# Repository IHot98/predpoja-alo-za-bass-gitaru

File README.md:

Predpojačalo za bass gitaru
---

***
Maturalni rad iz srednje škole 
Rađeno 2017. godine

Predpojačalo rastavljeno na više PCB-a radi modularnosti
***

slika pojačala u fazi izrade

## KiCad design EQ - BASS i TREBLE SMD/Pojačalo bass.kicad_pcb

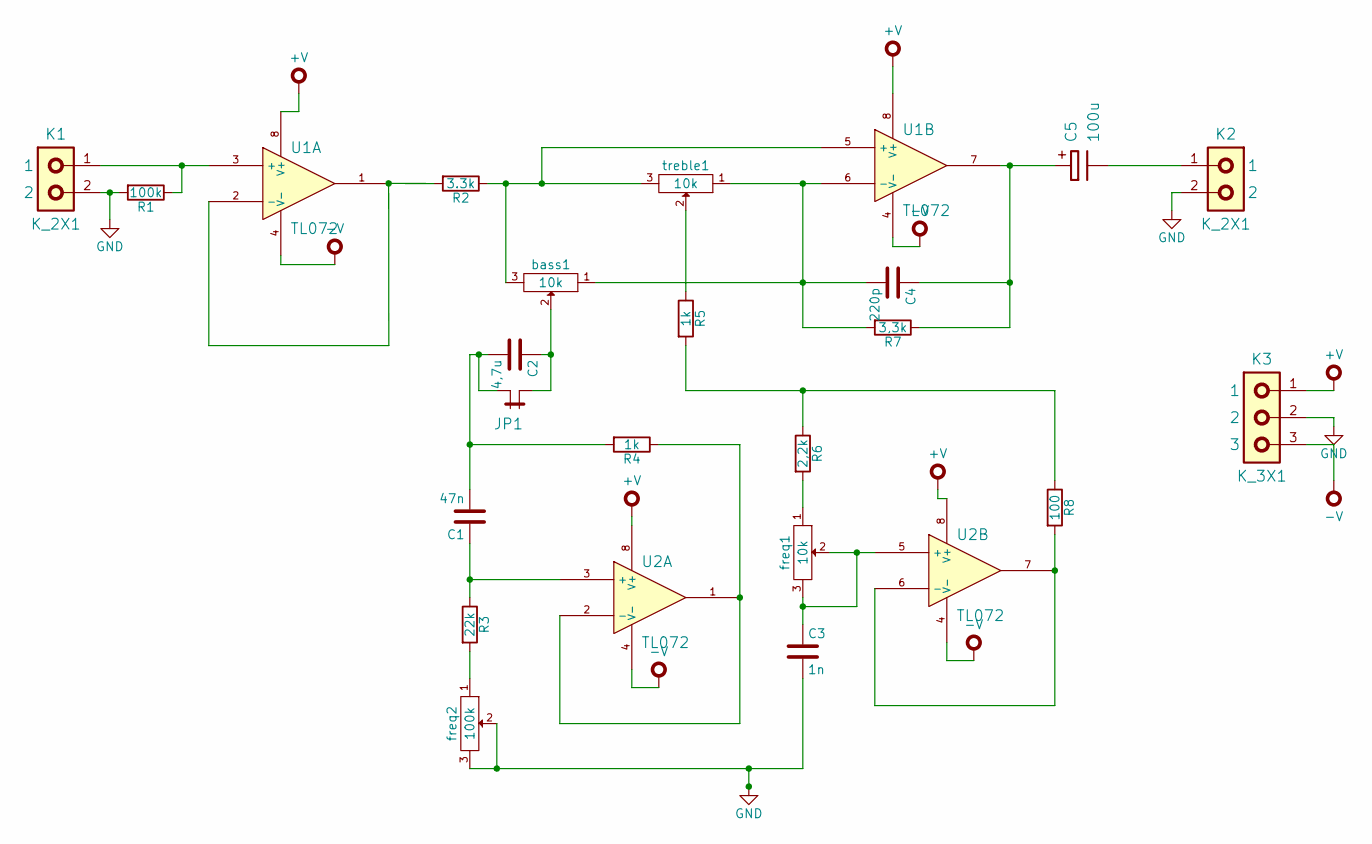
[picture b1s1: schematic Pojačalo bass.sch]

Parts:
C1: 47n; C_R5_D2,5X7,2
C2: 4,7u; C_R5_D2,5X7,2
C3: 1n; C_R5_D2,5X7,2
C4: 220p; C_R5_D2,5X7,2
C5: 100u; CPOL_R5_D6,35
JP1: JP; K_2X1_VERT_KV_R2,54
K1, K2: K_2X1; K_2x1
K3: K_3X1; K_3X1_VERT_KV_R2,54
R1: 100k; R_SMD_0805_NoSilk
R2: 3.3k; R_SMD_0805_NoSilk
R3: 22k; R_SMD_0805_NoSilk
R4, R5: 1k; R_SMD_0805_NoSilk
R6: 2,2k; R_SMD_0805_NoSilk
R7: 3,3k; R_SMD_0805_NoSilk
R8: 100; R_SMD_0805_NoSilk
U1, U2: TL072; DIP-8
bass1: 10k; K_3x1_PIN_R2,54
freq1: 10k; K_3x1_PIN_R2,54
freq2: 100k; K_3x1_PIN_R2,54
treble1: 10k; K_3x1_PIN_R2,54

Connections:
+V: K3.1, U1.8 (V+), U2.8 (V+)
-V: K3.3, U1.4 (V-), U2.4 (V-)
GND: C3.2, K1.2, K2.2, K3.2, R1.2, freq2.2, freq2.3
unnamed: C1.1, R3.1, U2.3 (+)
unnamed: C1.2, C2.2, JP1.2, R4.2
unnamed: C2.1, JP1.1, bass1.2
unnamed: C3.1, U2.5 (+), freq1.2, freq1.3
unnamed: C4.1, C5.+, R7.1, U1.7
unnamed: C4.2, R7.2, U1.6 (-), bass1.1, treble1.1
unnamed: C5.-, K2.1
unnamed: K1.1, R1.1, U1.3 (+)
unnamed: R2.1, U1.5 (+), bass1.3, treble1.3
unnamed: R2.2, U1.1, U1.2 (-)
unnamed: R3.2, freq2.1
unnamed: R4.1, U2.1, U2.2 (-)
unnamed: R5.1, treble1.2
unnamed: R5.2, R6.1, R8.1
unnamed: R6.2, freq1.1
unnamed: R8.2, U2.6 (-), U2.7

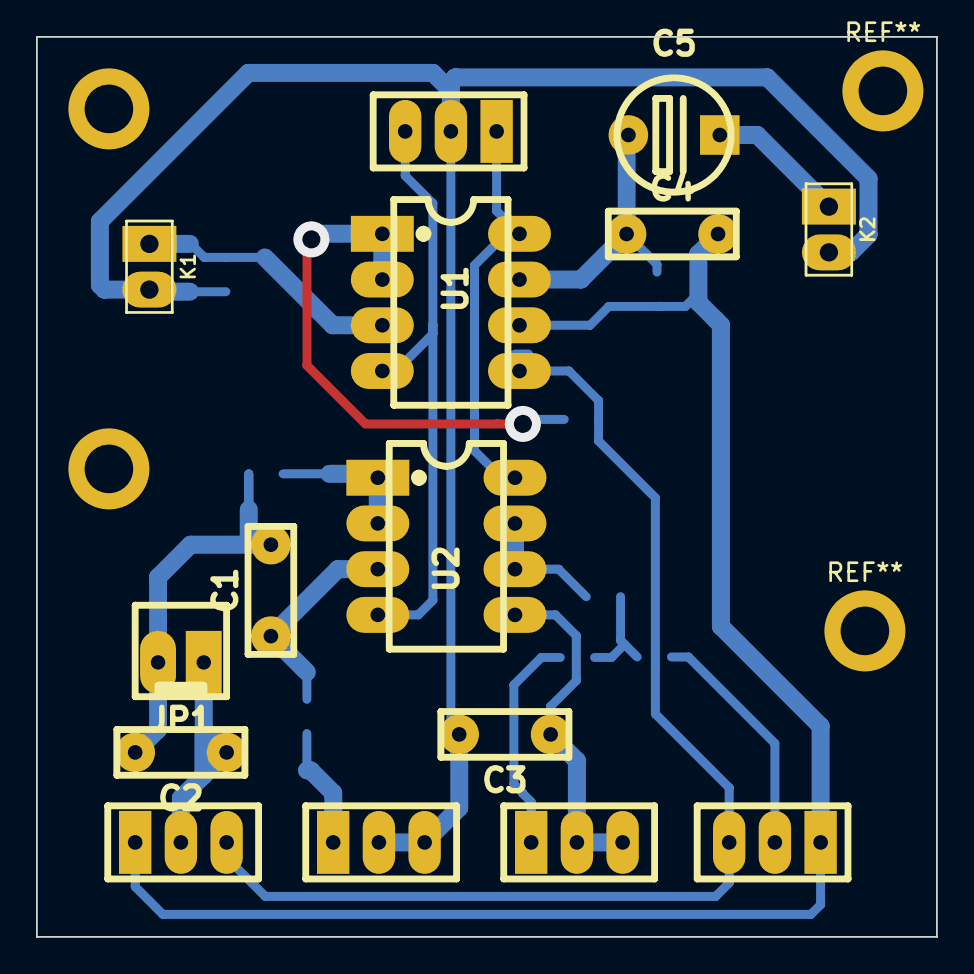
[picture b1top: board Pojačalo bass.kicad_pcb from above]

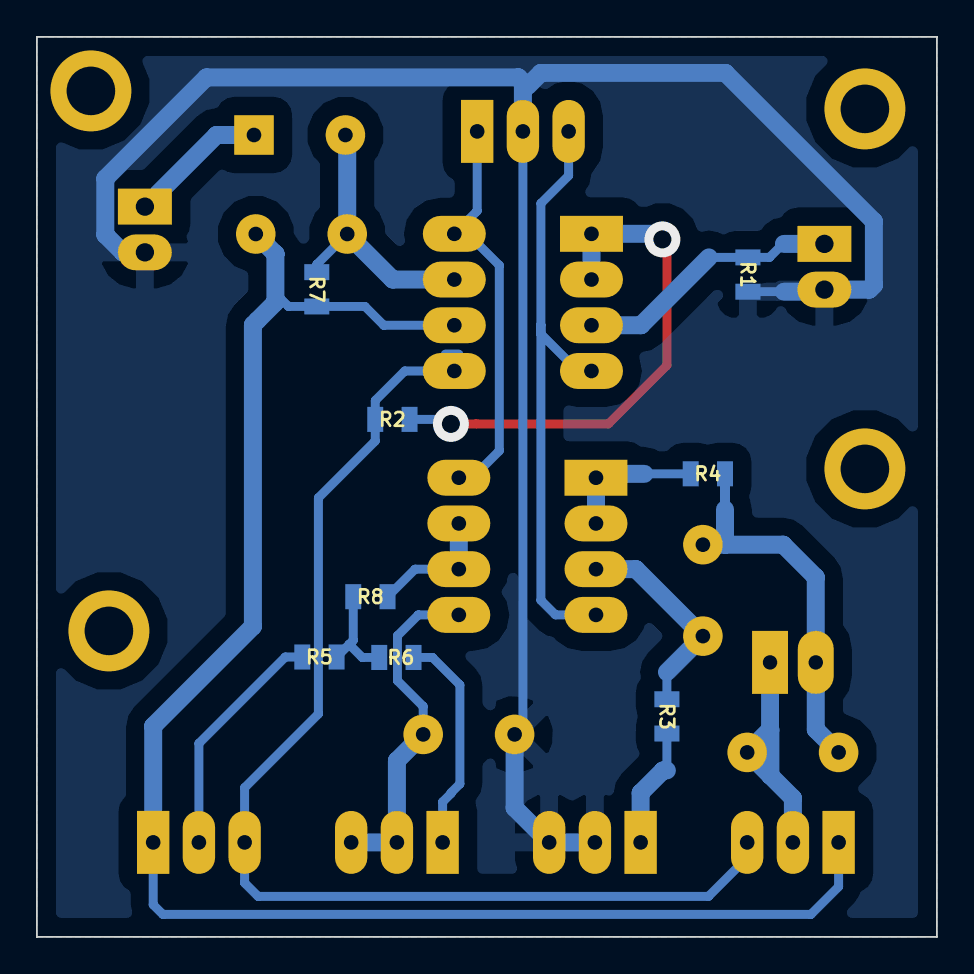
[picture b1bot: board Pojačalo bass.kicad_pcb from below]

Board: 2 copper layers, 50.0 x 50.0 mm, 23 parts (8 on the bottom side), 19 nets.

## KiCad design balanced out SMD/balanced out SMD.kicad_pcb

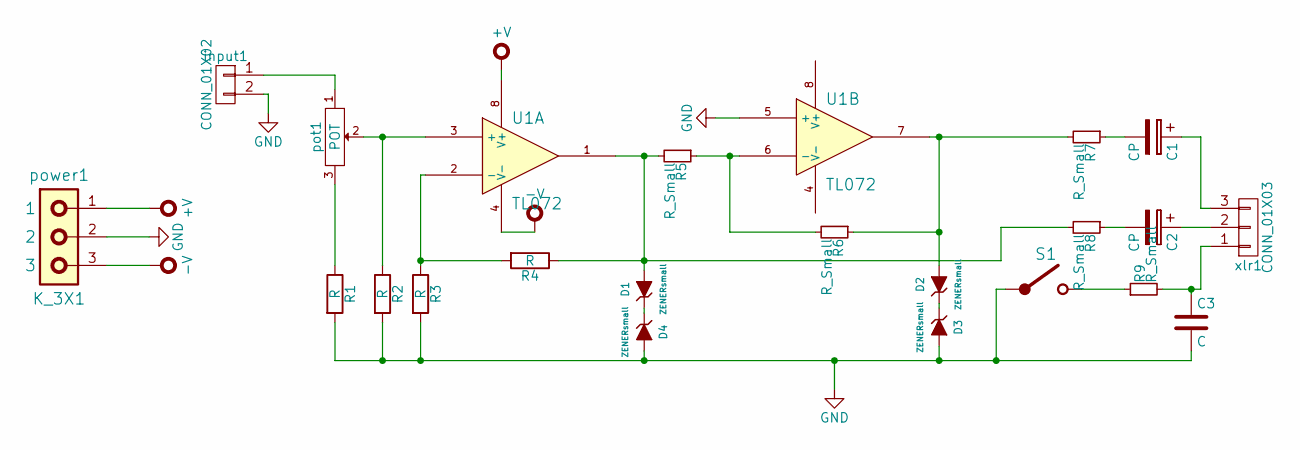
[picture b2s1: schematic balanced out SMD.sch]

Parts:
C1, C2: CP; C_Radial_D5_L6_P2.5
C3: C; C_Radial_D5_L6_P2.5
D1, D2, D3, D4: ZENERsmall; Diode_DO-35_SOD27_Horizontal_RM10
R1, R2, R3, R4: R; R_SMD_0805_NoSilk
R5, R6, R7, R8: R_Small; R_SMD_0805_NoSilk
R9: R_Small; R_MF_0,6W_R10
S1: S_1; K_2X1_VERT_KV_R2,54
U1: TL072; DIP-8
input1: CONN_01X02; K_2X1_VERT_KV_R2,54
pot1: POT; K_3X1_VERT_KV_R2,54
power1: K_3X1; K_3X1_VERT_KV_R2,54
xlr1: CONN_01X03; K_3X1_VERT_KV_R2,54

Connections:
+V: U1.8 (V+), power1.1
-V: U1.4 (V-), power1.3
GND: C3.2, D3.2 (A), D4.2 (A), R1.2, R2.2, R3.2, S1.1, U1.5 (+), input1.2, power1.2
unnamed: C1.1, xlr1.3
unnamed: C1.2, R7.1
unnamed: C2.1, xlr1.2
unnamed: C2.2, R8.1
unnamed: C3.1, R9.2, xlr1.1
unnamed: D1.1 (K), D4.1 (K)
unnamed: D1.2 (A), R4.1, R5.2, R8.2, U1.1
unnamed: D2.1 (K), D3.1 (K)
unnamed: D2.2 (A), R6.1, R7.2, U1.7
unnamed: R1.1, pot1.3
unnamed: R2.1, U1.3 (+), pot1.2
unnamed: R3.1, R4.2, U1.2 (-)
unnamed: R5.1, R6.2, U1.6 (-)
unnamed: R9.1, S1.2
unnamed: input1.1, pot1.1

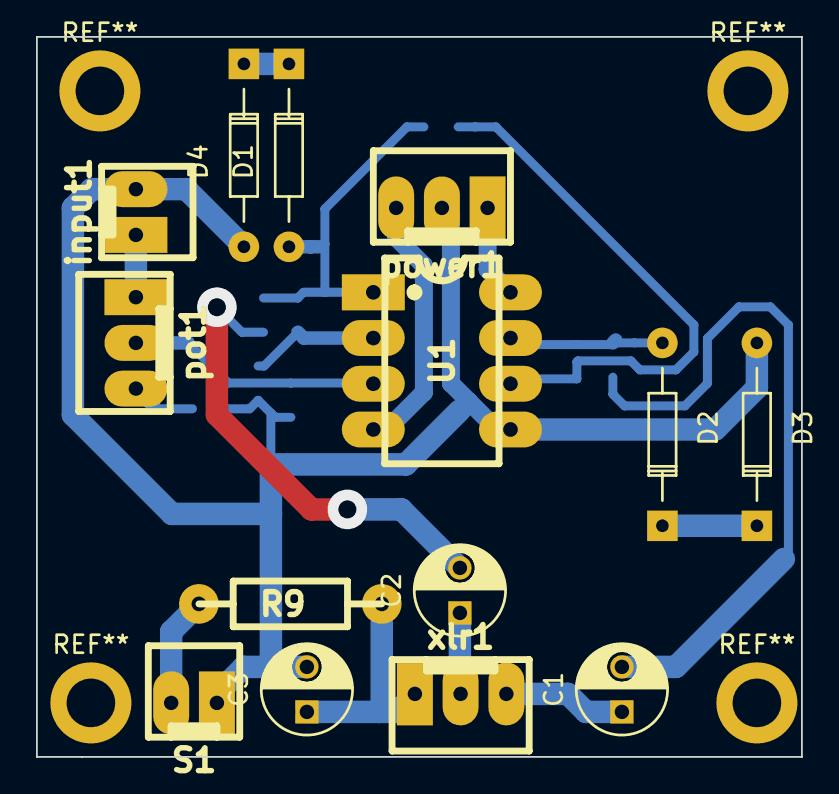
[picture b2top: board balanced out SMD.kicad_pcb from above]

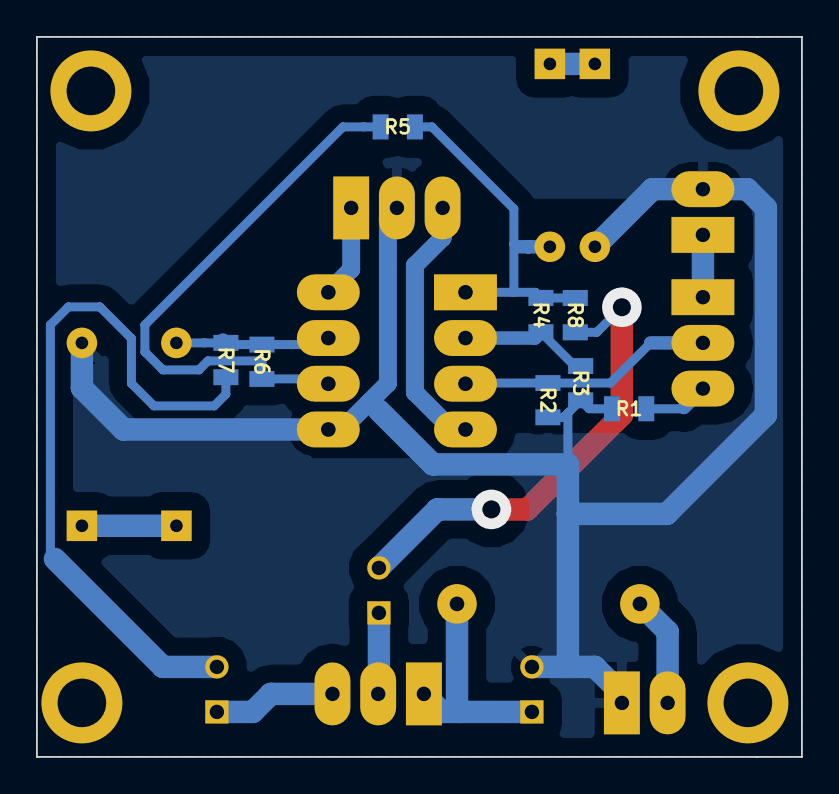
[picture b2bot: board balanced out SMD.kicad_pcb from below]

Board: 2 copper layers, 42.5 x 40.0 mm, 22 parts (8 on the bottom side), 18 nets.

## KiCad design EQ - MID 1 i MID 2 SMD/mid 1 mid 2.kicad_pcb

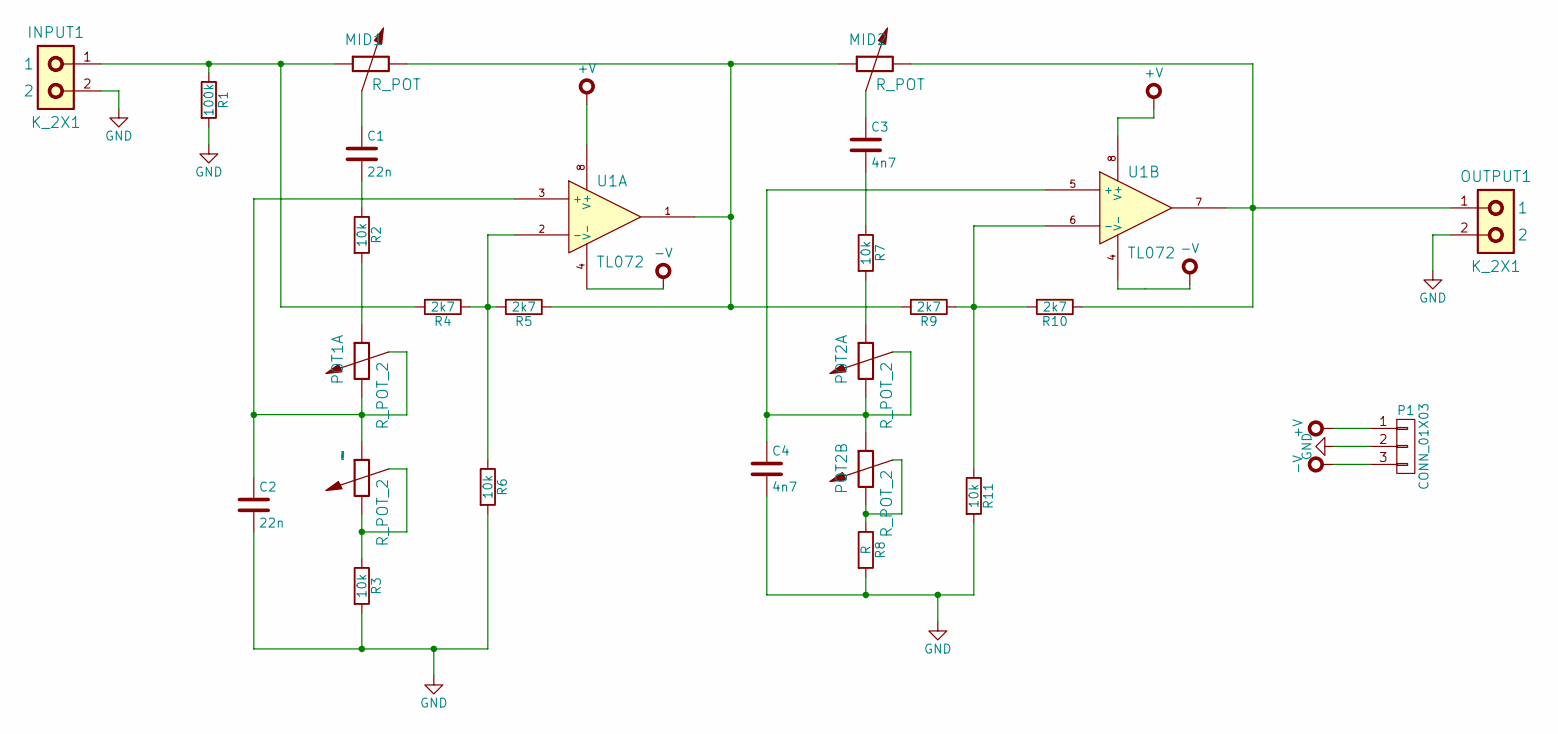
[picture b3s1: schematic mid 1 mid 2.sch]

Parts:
C1, C2: 22n; C_R5_D2,5X7,2
C3, C4: 4n7; C_R5_D2,5X7,2
INPUT1: K_2X1; K_2x1
MID1, MID2: R_POT; K_3X1_VERT_KV_R2,54
OUTPUT1: K_2X1; K_2x1
P1: CONN_01X03; K_3x1_PIN_R2,54
POT1, POT2: R_POT_2; K_3X2
R1: 100k; R_SMD_0805_NoSilk
R2, R3, R6, R7, R11: 10k; R_SMD_0805_NoSilk
R4, R5, R9, R10: 2k7; R_SMD_0805_NoSilk
R8: R; R_SMD_0805_NoSilk
U1: TL072; DIP-8

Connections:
+V: P1.1, U1.8 (V+)
-V: P1.3, U1.4 (V-)
GND: C2.2, C4.2, INPUT1.2, OUTPUT1.2, P1.2, R1.2, R3.2, R6.2, R8.2, R11.2
unnamed: C1.1, MID1.2
unnamed: C1.2, R2.1
unnamed: C2.1, U1.3 (+)
unnamed: C3.1, MID2.2
unnamed: C3.2, R7.1
unnamed: C4.1, POT2.2, POT2.3, POT2.4, U1.5 (+)
unnamed: INPUT1.1, MID1.1, R1.1, R4.2
unnamed: MID1.3, MID2.1, R5.1, R9.2, U1.1
unnamed: MID2.3, OUTPUT1.1, R10.1, U1.7
unnamed: POT1.1, R2.2
unnamed: POT1.2, POT1.3, POT1.4
unnamed: POT1.5, POT1.6, R3.1
unnamed: POT2.1, R7.2
unnamed: POT2.5, POT2.6, R8.1
unnamed: R4.1, R5.2, R6.1, U1.2 (-)
unnamed: R9.1, R10.2, R11.1, U1.6 (-)

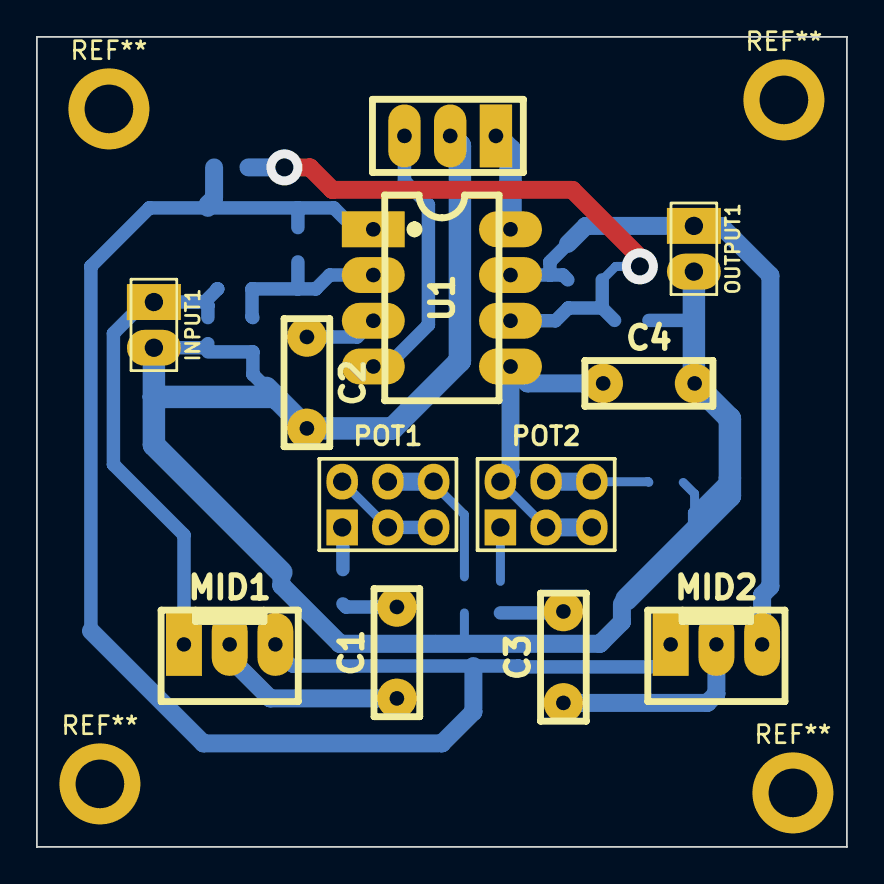
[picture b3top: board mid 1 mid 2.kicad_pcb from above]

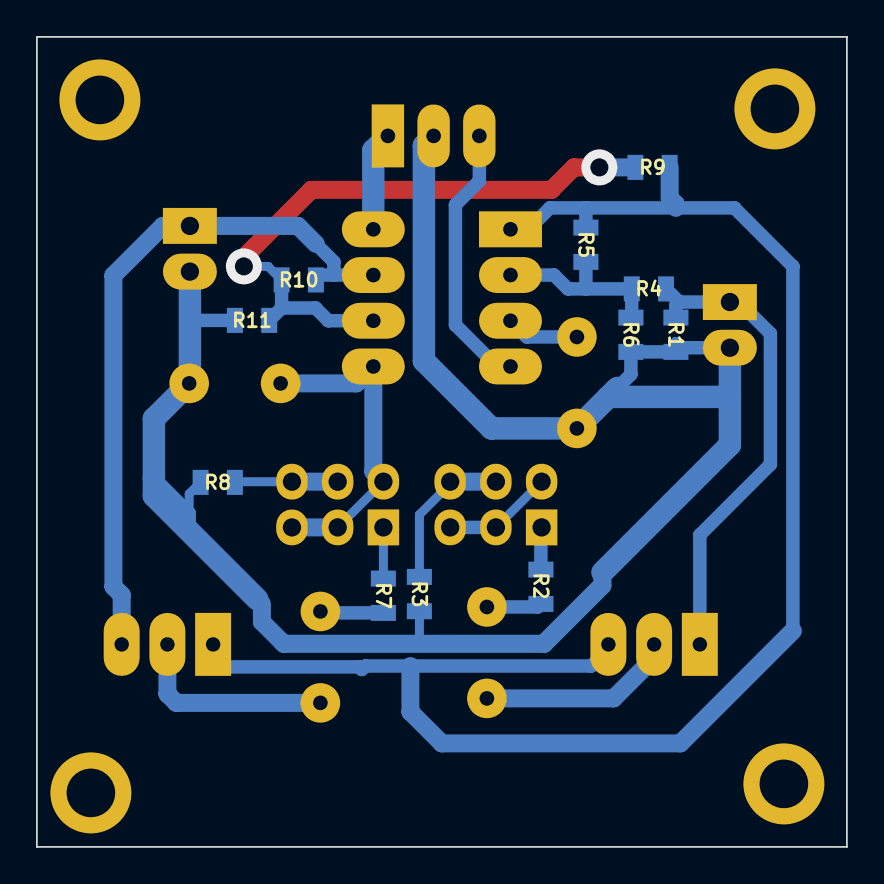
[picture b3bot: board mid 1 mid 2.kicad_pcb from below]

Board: 2 copper layers, 45.0 x 45.0 mm, 23 parts (11 on the bottom side), 19 nets.

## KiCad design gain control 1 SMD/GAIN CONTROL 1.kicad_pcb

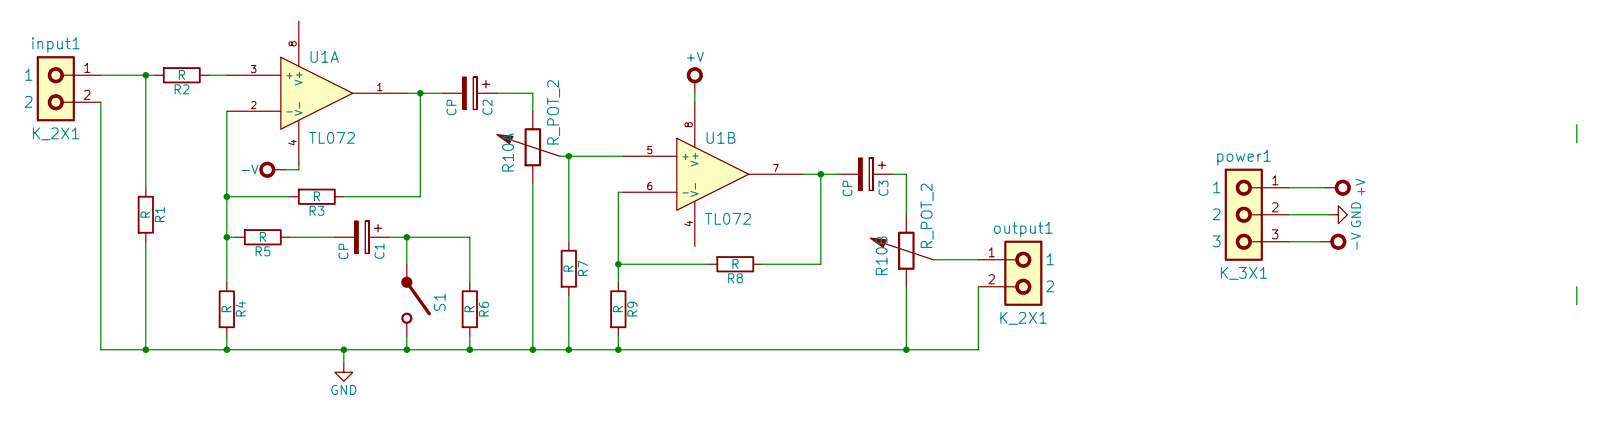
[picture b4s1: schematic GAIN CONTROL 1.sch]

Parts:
C1, C2, C3: CP; C_Radial_D6.3_L11.2_P2.5
R1, R2, R3, R4, R5, R6, R7, R8, R9: R; R_SMD_0805_NoSilk
R10: R_POT_2; K_3X2
S1: S_1; K_2x1
U1: TL072; DIP-8
input1: K_2X1; K_2x1
output1: K_2X1; K_2x1
power1: K_3X1; K_3x1_PIN_R2,54

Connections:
+V: U1.8 (V+), power1.1
-V: U1.4 (V-), power1.3
GND: R1.2, R4.2, R6.2, R7.2, R9.2, R10.1, R10.4, S1.2, input1.2, output1.2, power1.2
unnamed: C1.1, R6.1, S1.1
unnamed: C1.2, R5.1
unnamed: C2.1, R10.3
unnamed: C2.2, R3.1, U1.1
unnamed: C3.1, R10.6
unnamed: C3.2, R8.1, U1.7
unnamed: R1.1, R2.2, input1.1
unnamed: R2.1, U1.3 (+)
unnamed: R3.2, R4.1, R5.2, U1.2 (-)
unnamed: R8.2, R9.1, U1.6 (-)
unnamed: R7.1, R10.2, U1.5 (+)
unnamed: R10.5, output1.1

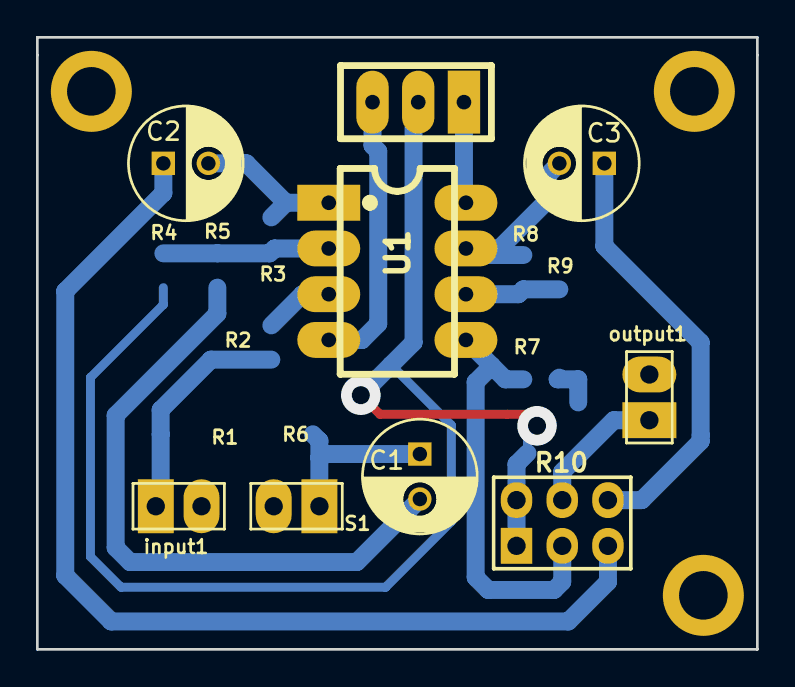
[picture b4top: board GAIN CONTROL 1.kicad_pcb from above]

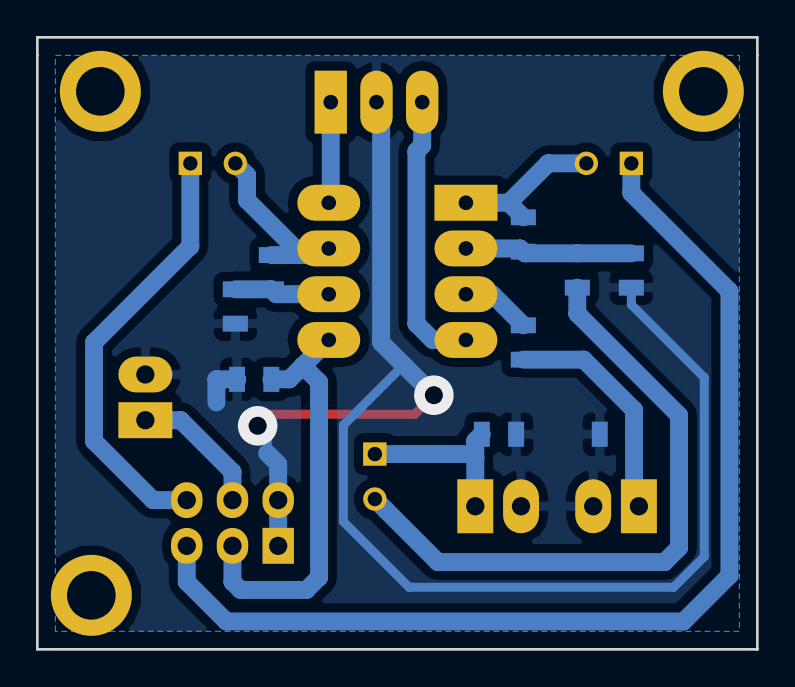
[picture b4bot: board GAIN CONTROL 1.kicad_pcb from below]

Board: 2 copper layers, 40.0 x 34.0 mm, 18 parts (9 on the bottom side), 15 nets.

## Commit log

2021-07-13 readme
